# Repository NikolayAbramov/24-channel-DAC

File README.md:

# 24-channel DAC
This is hardware project of a 24-channel DAC with isolated output controlled via Ethernet interface. 

# Specs
- Number of outputs: 24
- Resolution: 10 bit
- Output voltage: from -4.096 V to +4.096 V
- Output current: 10 mA max
- Output configuration: 24 channels with common rail, isolated from power supply
- Control: Ethernet with web interface and SCPI commands
- Power: 12V

# Details
The schematics and PCB files can be found in the /kicad folder, they are created using KiCAD. The schematics are also presented in PDF. There are 2 boards: the controller bord and the DAC board. The controller board contains a STM32 MCU, an isolated power coverter and an Ethernet PHY module. An of-the-shelf ENC28J60 module is used for the Ethernet. The DAC board is connected via isolated I2C and contains four 8-channel DAC ICs, reference source and output buffers.

The firmware for STM32 MCU can be found in the /STM32_firmware folder. The project is for STM32CubeIDE.

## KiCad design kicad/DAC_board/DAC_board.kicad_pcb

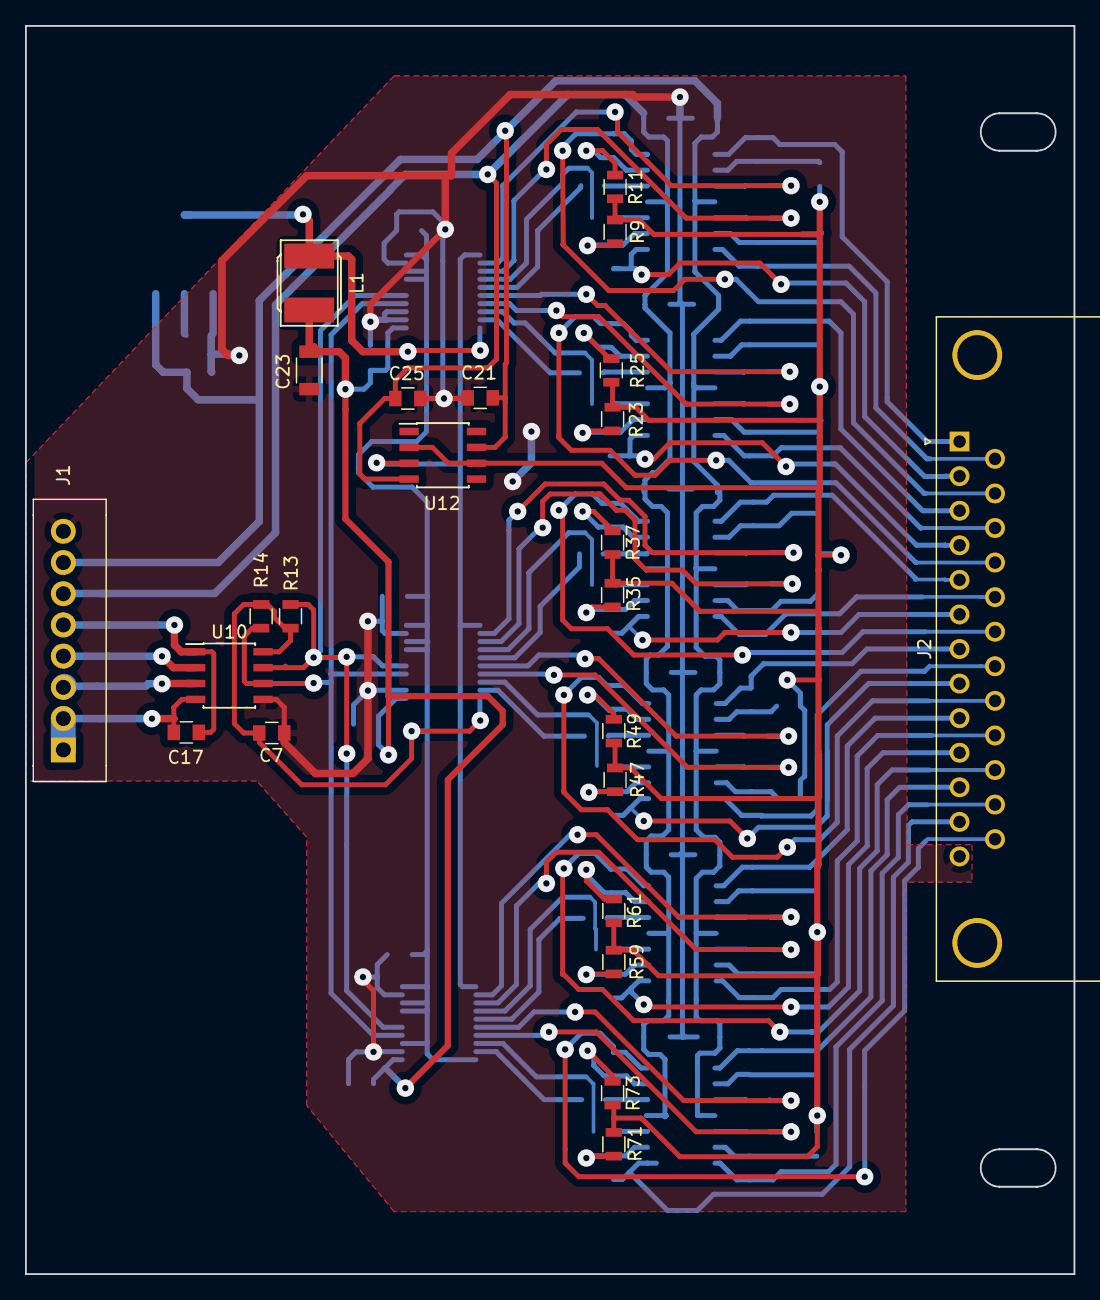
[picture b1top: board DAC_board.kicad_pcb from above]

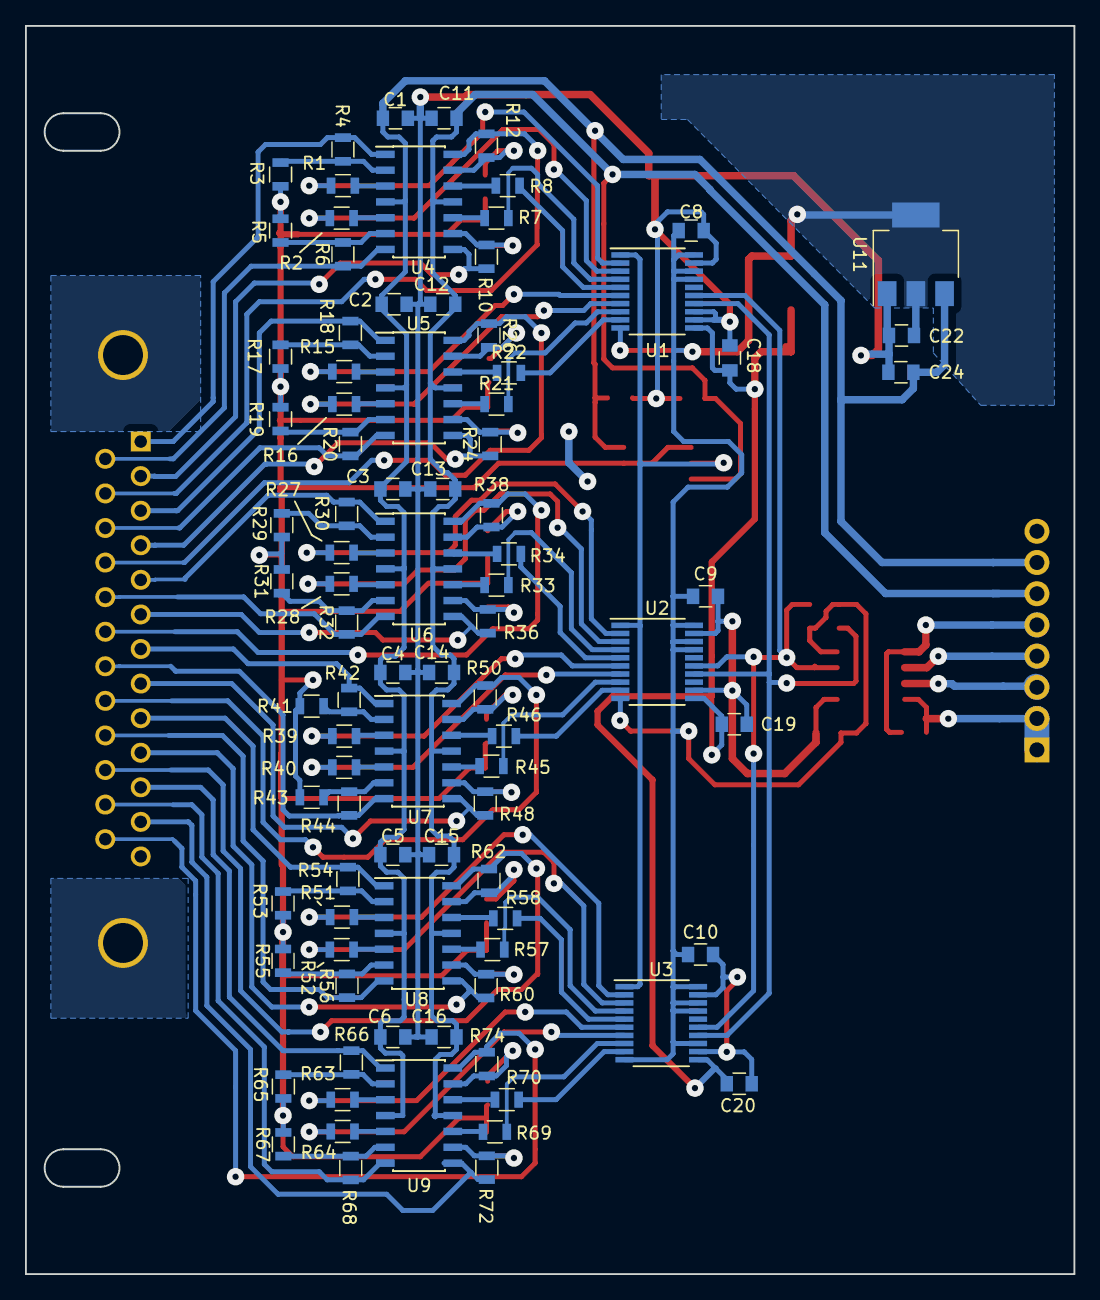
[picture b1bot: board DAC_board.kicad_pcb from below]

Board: 2 copper layers, 84.0 x 100.0 mm, 114 parts (90 on the bottom side), 109 nets.

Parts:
C1, C2, C3, C4, C5, C6, C7, C8, C9, C10, C11, C12, C13, C14, C15, C16, C17, C18, C19, C20, C21, C22, C24, C25: C; C_0805
C23: C; C_1206
J1: CONN_01X08; Wafer_Vertical22.5x5.8x7RM2.5-8
J2: DB25_FEMALE_MountingHoles; DSUB-25_Female_Horizontal_P2.77x2.84mm_EdgePinOffset9.90mm_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
L1: L; Choke_SMD_Taiyo_NRS50XX-Handsoldering
R1, R2, R3, R4, R5, R6, R7, R8, R9, R10, R11, R12, R13, R14, R15, R16, R17, R18, R19, R20, R21, R22, R23, R24, R25, R26, R27, R28, R29, R30, R31, R32, R33, R34, R35, R36, R37, R38, R39, R40, R41, R42, R43, R44, R45, R46, R47, R48, R49, R50, R51, R52, R53, R54, R55, R56, R57, R58, R59, R60, R61, R62, R63, R64, R65, R66, R67, R68, R69, R70, R71, R72, R73, R74: R; R_0805
U1, U2, U3: MAX5825; TSSOP-20_4.4x6.5mm_Pitch0.65mm
U4, U5, U6, U7, U8, U9: LM324; SOIC-14_3.9x8.7mm_Pitch1.27mm
U10: ADUM1251; SOIC-8_3.9x4.9mm_Pitch1.27mm
U11: LM1117-5.0; SOT-223
U12: OP1177; SOIC-8_3.9x4.9mm_Pitch1.27mm

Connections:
+5V: C7.1, C8.1, C9.1, C10.1, C22.1, L1.1, R13.1, R14.1, U1.10, U1.17, U1.18, U1.20, U2.10, U2.17, U2.18, U2.20, U3.10, U3.13, U3.17, U3.18, U3.20, U10.8, U11.2, U11.4
+5VA: C18.1, C19.1, C20.1, C23.1, L1.2, U1.11, U2.11, U3.11
/0: R1.2, U1.2
/1: R2.2, U1.3
/2: R7.2, U1.4
/3: R8.2, U1.5
/4: R15.2, U1.6
/5: R16.2, U1.7
/6: R21.2, U1.8
/7: R22.2, U1.9
/8: R27.2, U2.2
/9: R28.2, U2.3
/10: R33.2, U2.4
/11: R34.2, U2.5
/12: R39.2, U2.6
/13: R40.2, U2.7
/14: R45.2, U2.8
/15: R46.2, U2.9
/16: R51.2, U3.2
/17: R52.2, U3.3
/18: R57.2, U3.4
/19: R58.2, U3.5
/20: R63.2, U3.6
/21: R64.2, U3.7
/22: R69.2, U3.8
/23: R70.2, U3.9
/SCL: R14.2, U1.14, U2.14, U3.14, U10.6
/SDA: R13.2, U1.15, U2.15, U3.15, U10.7
/out0: J2.1, R4.1, U4.1
/out1: J2.14, R6.1, U4.7
/out2: J2.2, R10.1, U4.8
/out3: J2.15, R12.1, U4.14
/out4: J2.3, R18.1, U5.1
/out5: J2.16, R20.1, U5.7
/out6: J2.4, R24.1, U5.8
/out7: J2.17, R26.1, U5.14
/out8: J2.5, R30.1, U6.1
/out9: J2.18, R32.1, U6.7
/out10: J2.6, R36.1, U6.8
/out11: J2.19, R38.1, U6.14
/out12: J2.7, R42.1, U7.1
/out13: J2.20, R44.1, U7.7
/out14: J2.8, R48.1, U7.8
/out15: J2.21, R50.1, U7.14
/out16: J2.9, R54.1, U8.1
/out17: J2.22, R56.1, U8.7
/out18: J2.10, R60.1, U8.8
/out19: J2.23, R62.1, U8.14
/out20: J2.11, R66.1, U9.1
/out21: J2.24, R68.1, U9.7
/out22: J2.12, R72.1, U9.8
/out23: J2.25, R74.1, U9.14
/ref: U1.1, U2.1, U3.1, U12.3
GNDA: C1.2, C2.2, C3.2, C4.2, C5.2, C6.2, C7.2, C8.2, C9.2, C10.2, C11.1, C12.1, C13.1, C14.1, C15.1, C16.1, C18.2, C19.2, C20.2, C21.2, C22.2, C23.2, C24.2, C25.1, J1.8, J2.13, U1.12, U1.13, U1.19, U2.12, U2.19, U3.12, U3.19, U10.5, U11.1
unnamed: C17.1, J1.1, J1.2, U10.4
unnamed: C17.2, J1.5, U10.1
unnamed: J1.3, U10.3
unnamed: J1.4, U10.2
unnamed: R1.1, U4.3
unnamed: R2.1, U4.5
unnamed: R3.1, R4.2, U4.2
unnamed: R5.1, R6.2, U4.6
unnamed: R7.1, U4.10
unnamed: R8.1, U4.12
unnamed: R9.1, R10.2, U4.9
unnamed: R11.1, R12.2, U4.13
unnamed: R15.1, U5.3
unnamed: R16.1, U5.5
unnamed: R17.1, R18.2, U5.2
unnamed: R19.1, R20.2, U5.6
unnamed: R21.1, U5.10
unnamed: R22.1, U5.12
unnamed: R23.1, R24.2, U5.9
unnamed: R25.1, R26.2, U5.13
unnamed: R27.1, U6.3
unnamed: R28.1, U6.5
unnamed: R29.1, R30.2, U6.2
unnamed: R31.1, R32.2, U6.6
unnamed: R33.1, U6.10
unnamed: R34.1, U6.12
unnamed: R35.1, R36.2, U6.9
unnamed: R37.1, R38.2, U6.13
unnamed: R39.1, U7.3
unnamed: R40.1, U7.5
unnamed: R41.1, R42.2, U7.2
unnamed: R43.1, R44.2, U7.6
unnamed: R45.1, U7.10
unnamed: R46.1, U7.12
unnamed: R47.1, R48.2, U7.9
unnamed: R49.1, R50.2, U7.13
unnamed: R51.1, U8.3
unnamed: R52.1, U8.5
unnamed: R53.1, R54.2, U8.2
unnamed: R55.1, R56.2, U8.6
unnamed: R57.1, U8.10
unnamed: R58.1, U8.12
unnamed: R59.1, R60.2, U8.9
unnamed: R61.1, R62.2, U8.13
unnamed: R63.1, U9.3
unnamed: R64.1, U9.5
unnamed: R65.1, R66.2, U9.2
unnamed: R67.1, R68.2, U9.6
unnamed: R69.1, U9.10
unnamed: R70.1, U9.12
unnamed: R71.1, R72.2, U9.9
unnamed: R73.1, R74.2, U9.13
REF_BUF: R3.2, R5.2, R9.2, R11.2, R17.2, R19.2, R23.2, R25.2, R29.2, R31.2, R35.2, R37.2, R41.2, R43.2, R47.2, R49.2, R53.2, R55.2, R59.2, R61.2, R65.2, R67.2, R71.2, R73.2, U12.2, U12.6
V+: C1.1, C2.1, C3.1, C4.1, C5.1, C6.1, C21.1, C24.1, J1.7, U4.4, U5.4, U6.4, U7.4, U8.4, U9.4, U11.3, U12.7
V-: C11.2, C12.2, C13.2, C14.2, C15.2, C16.2, C25.2, J1.6, U4.11, U5.11, U6.11, U7.11, U8.11, U9.11, U12.4

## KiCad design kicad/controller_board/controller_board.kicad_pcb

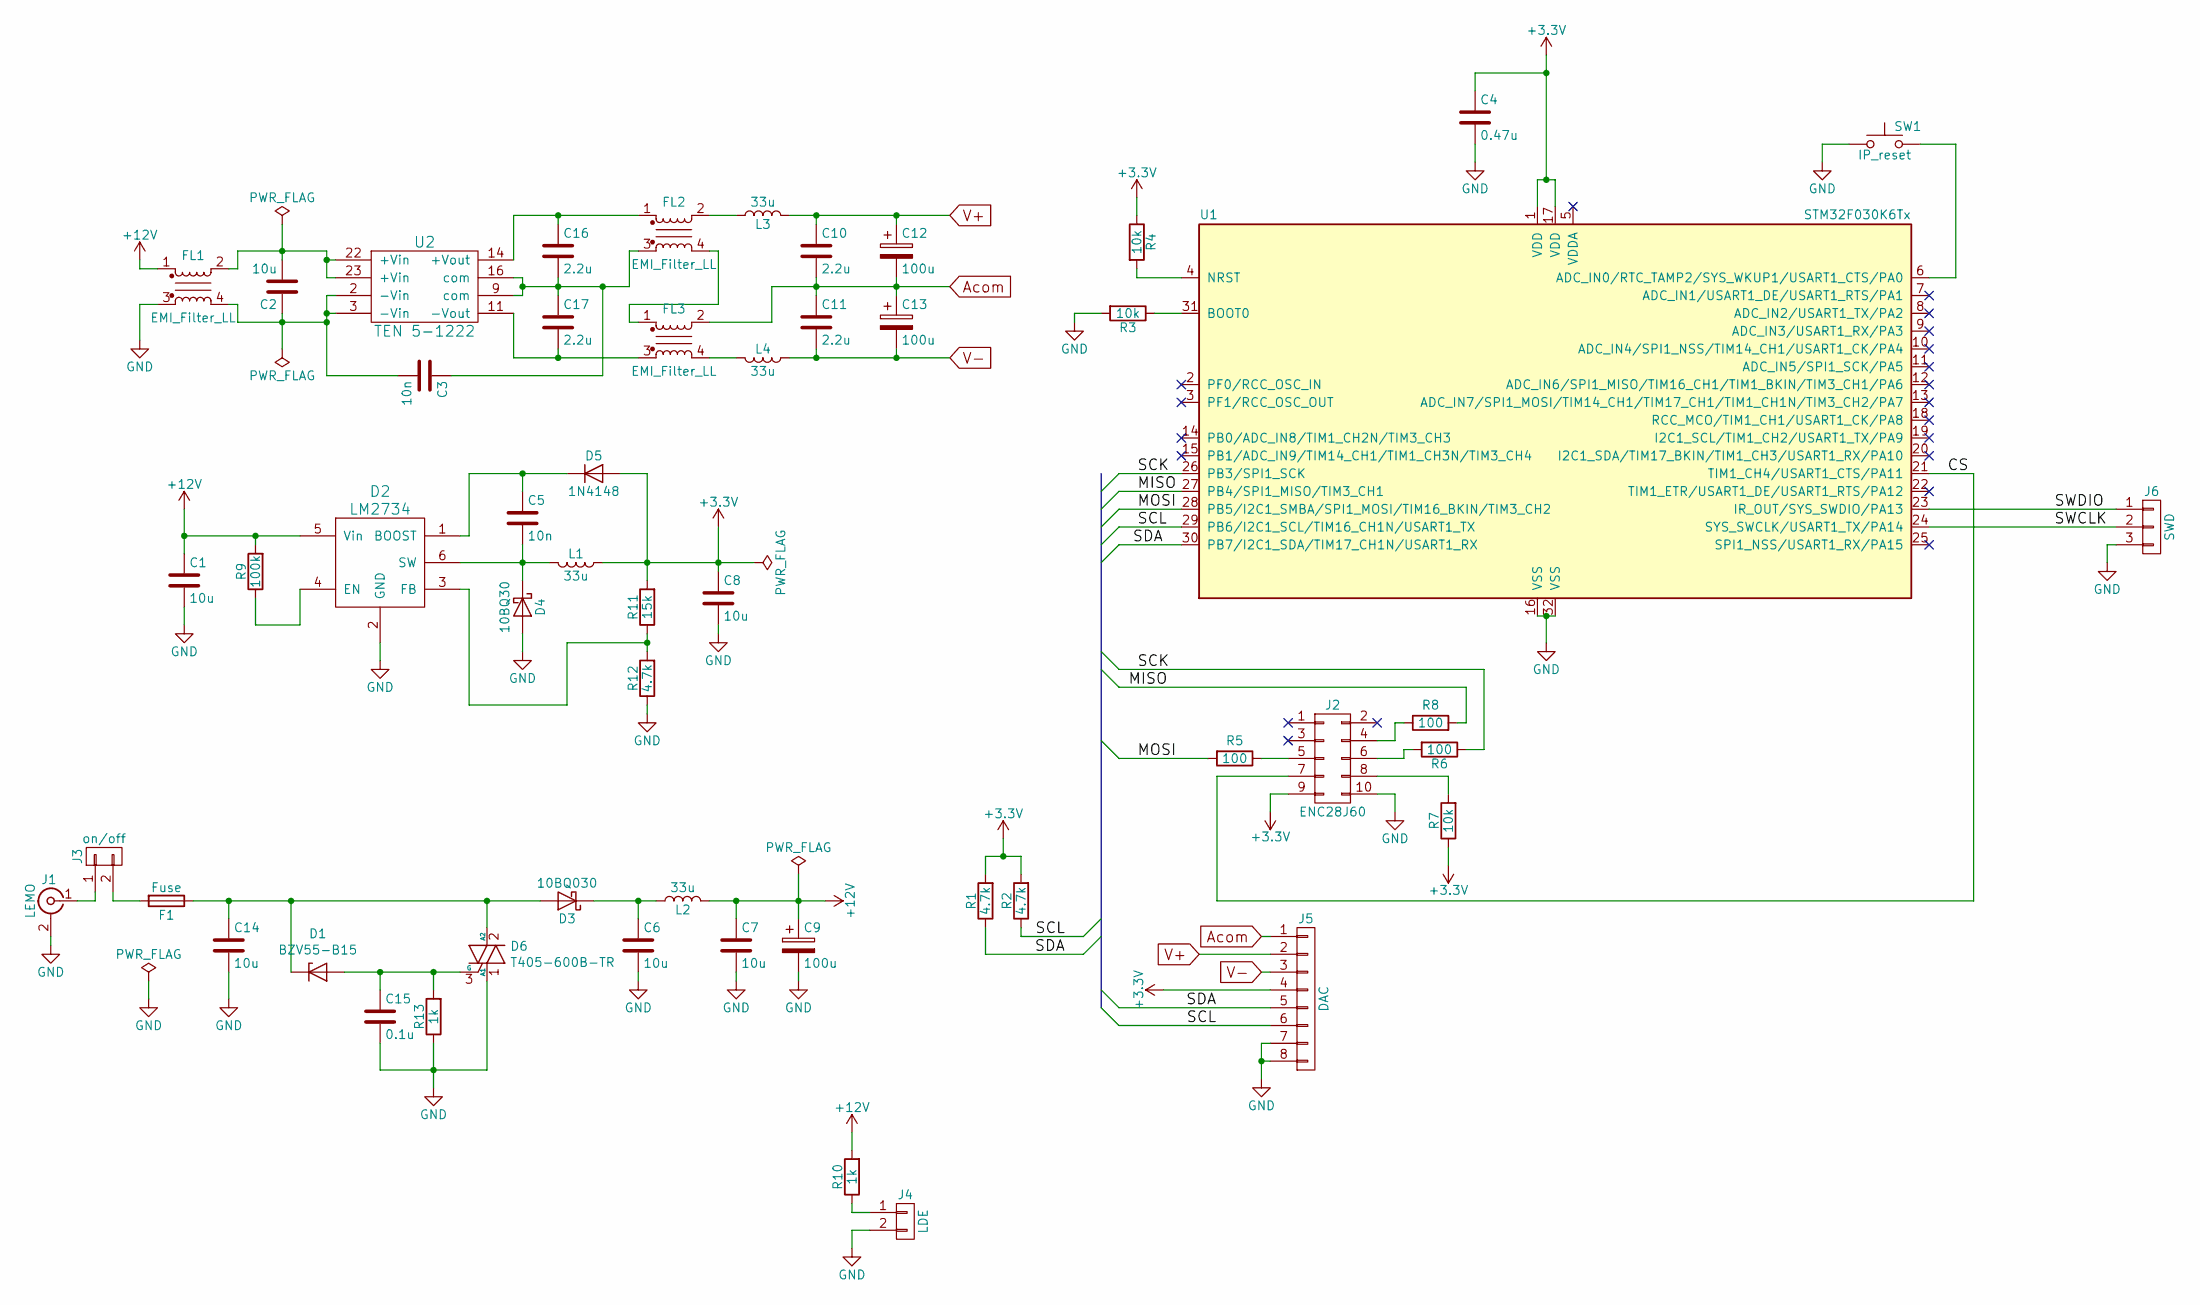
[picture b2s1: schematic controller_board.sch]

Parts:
C1, C2, C6, C7, C8: 10u; C_1206
C3, C5: 10n; C_1206
C4: 0.47u; C_0805
C9, C12, C13: 100u; CP_Tantalum_Case-D_EIA-7343-31_Hand
C10, C11, C16, C17: 2.2u; C_1206
C14: 10u; C_1210
C15: 0.1u; C_0805
D1: BZV55-B15; D_1206
D2: LM2734; SuperSOT-6
D3: 10BQ030; D_SMB
D4: 10BQ30; D_SMB
D5: 1N4148; D_SOD-123
D6: T405-600B-TR; TO-252-2
F1: Fuse; FH-101
FL1, FL2, FL3: EMI_Filter_LL; Bourns_B82790
J1: LEMO; LEMO_00_R
J2: ENC28J60; ENC28J60_module
J3: on/off; Pin_Header_Straight_1x02_Pitch2.54mm
J4: LDE; Pin_Header_Straight_1x02_Pitch2.54mm
J5: DAC; Wafer_Vertical22.5x5.8x7RM2.5-8
J6: SWD; Pin_Header_Straight_1x03_Pitch2.54mm
L1, L2, L3, L4: 33u; SRR0603
R1, R2, R12: 4.7k; R_0805
R3, R4, R7: 10k; R_0805
R5, R6, R8: 100; R_0805
R9: 100k; R_0805
R10, R13: 1k; R_0805
R11: 15k; R_0805
SW1: IP_reset; SW_Tactile_SPST_Angled_PTS645Vx39-2LFS
U1: STM32F030K6Tx; QFP_32
U2: TEN 5-1222; Traco_TEN5

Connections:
+3V3: C4.1, C8.1, D5.2 (A), J2.9, J5.4, L1.1, R1.2, R2.2, R4.1, R7.1, R11.2, U1.1 (VDD), U1.17 (VDD)
+12V: C1.1, C7.1, C9.1, D2.5 (Vin), FL1.1, L2.2, R9.2, R10.2
/CS: J2.7, U1.21 (TIM1_CH4/USART1_CTS/PA11)
/MISO: R8.2, U1.27 (PB4/SPI1_MISO/TIM3_CH1)
/MOSI: R5.2, U1.28 (PB5/I2C1_SMBA/SPI1_MOSI/TIM16_BKIN/TIM3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)
/SCK: R6.1, U1.26 (PB3/SPI1_SCK)
/SCL: J5.6, R2.1, U1.29 (PB6/I2C1_SCL/TIM16_CH1N/USART1_TX)
/SDA: J5.5, R1.1, U1.30 (PB7/I2C1_SDA/TIM17_CH1N/USART1_RX)
/SWCLK: J6.2, U1.24 (SYS_SWCLK/USART1_TX/PA14)
/SWDIO: J6.1, U1.23 (IR_OUT/SYS_SWDIO/PA13)
Acom: C10.2, C11.1, C12.2, C13.1, FL3.2, J5.1
GND: C1.2, C4.2, C6.2, C7.2, C8.2, C9.2, C14.2, C15.2, D2.2 (GND), D4.2 (A), D6.1 (A1), FL1.3, J1.2 (Ext), J2.10, J4.2, J5.7, J5.8, J6.3, R3.2, R12.1, R13.1, SW1.1, U1.16 (VSS), U1.32 (VSS)
unnamed: C2.1, C3.2, FL1.4, U2.2 (-Vin), U2.3 (-Vin)
unnamed: C2.2, FL1.2, U2.22 (+Vin), U2.23 (+Vin)
unnamed: C5.1, D2.1 (BOOST), D5.1 (K)
unnamed: C5.2, D2.6 (SW), D4.1 (K), L1.2
unnamed: C6.1, D3.1 (K), L2.1
unnamed: C14.1, D1.1 (K), D3.2 (A), D6.2 (A2), F1.1
unnamed: C15.1, D1.2 (A), D6.3 (G), R13.2
unnamed: C16.1, FL2.1, U2.14 (+Vout)
unnamed: C3.1, C16.2, C17.1, FL2.3, U2.9 (com), U2.16 (com)
unnamed: C17.2, FL3.3, U2.11 (-Vout)
unnamed: D2.3 (FB), R11.1, R12.2
unnamed: D2.4 (EN), R9.1
unnamed: F1.2, J3.2
unnamed: FL2.2, L3.1
unnamed: FL2.4, FL3.1
unnamed: FL3.4, L4.2
unnamed: J1.1 (In), J3.1
unnamed: J2.4, R8.1
unnamed: J2.5, R5.1
unnamed: J2.6, R6.2
unnamed: J2.8, R7.2
unnamed: J4.1, R10.1
unnamed: R3.1, U1.31 (BOOT0)
unnamed: R4.2, U1.4 (NRST)
unnamed: SW1.2, U1.6 (ADC_IN0/RTC_TAMP2/SYS_WKUP1/USART1_CTS/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)
V+: C10.1, C12.1, J5.2, L3.2
V-: C11.2, C13.2, J5.3, L4.1

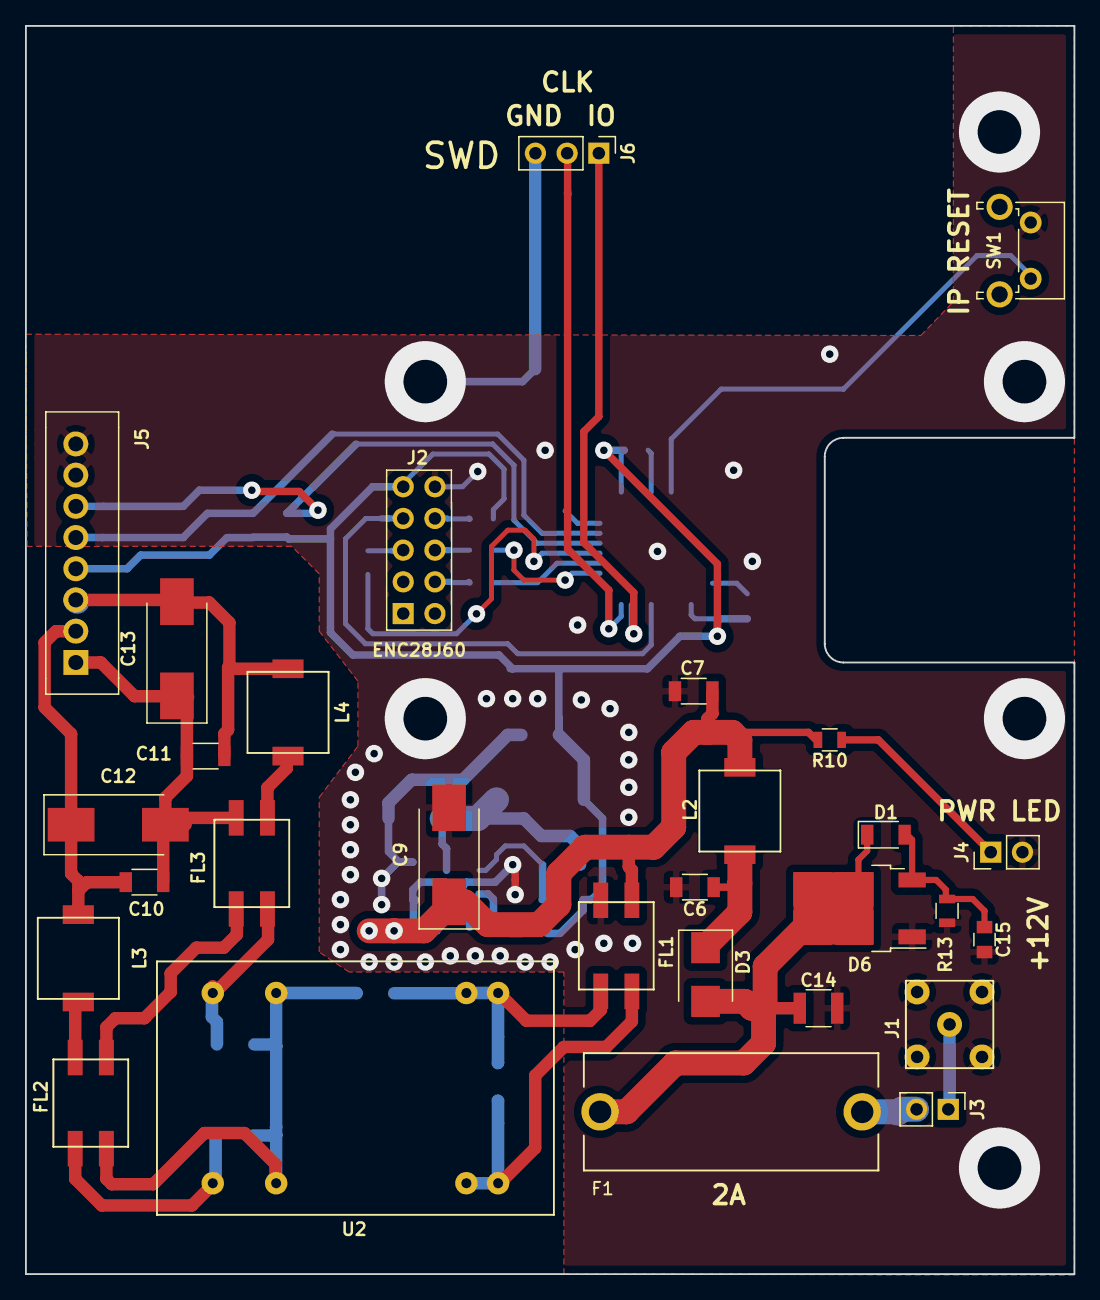
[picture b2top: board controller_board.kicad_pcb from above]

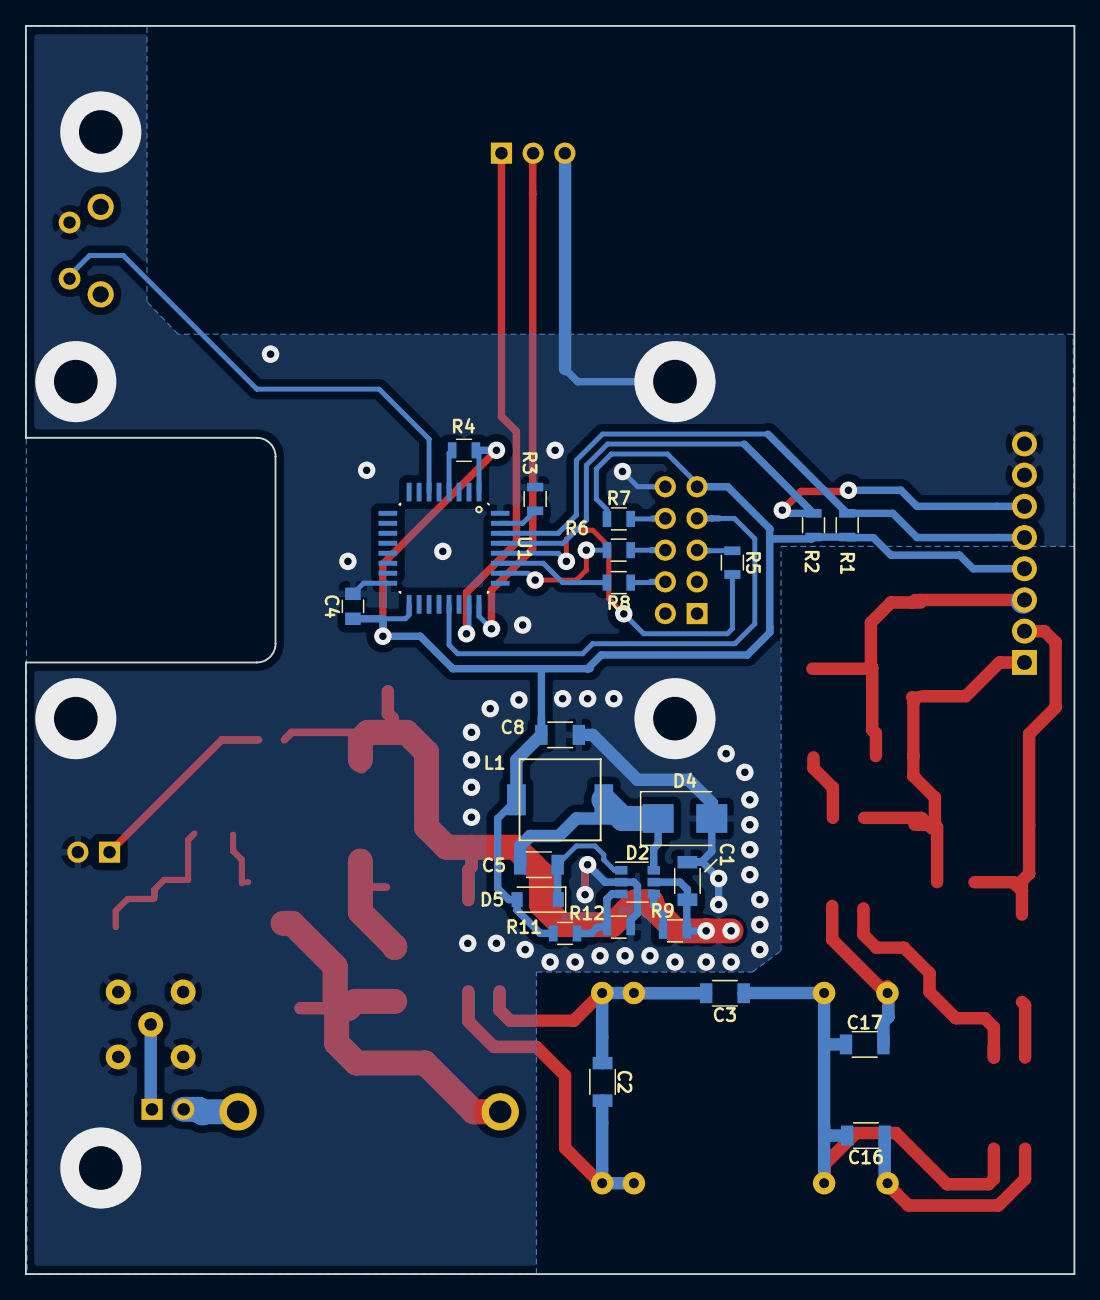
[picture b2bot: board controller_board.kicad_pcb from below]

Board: 2 copper layers, 84.0 x 100.0 mm, 53 parts (24 on the bottom side), 39 nets.

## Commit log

2022-12-11 first
2022-12-11 readme
2022-12-11 Saved README.md with Dillinger.io
2022-12-11 new file: kicad/DAC_board/DAC_board.kicad_prl new file: kicad/DAC_board/DAC_board.kicad_pro new file: kicad/DAC_board/DAC_board.pdf new file: kicad/controller_board/controller_board.kicad_prl new fil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
